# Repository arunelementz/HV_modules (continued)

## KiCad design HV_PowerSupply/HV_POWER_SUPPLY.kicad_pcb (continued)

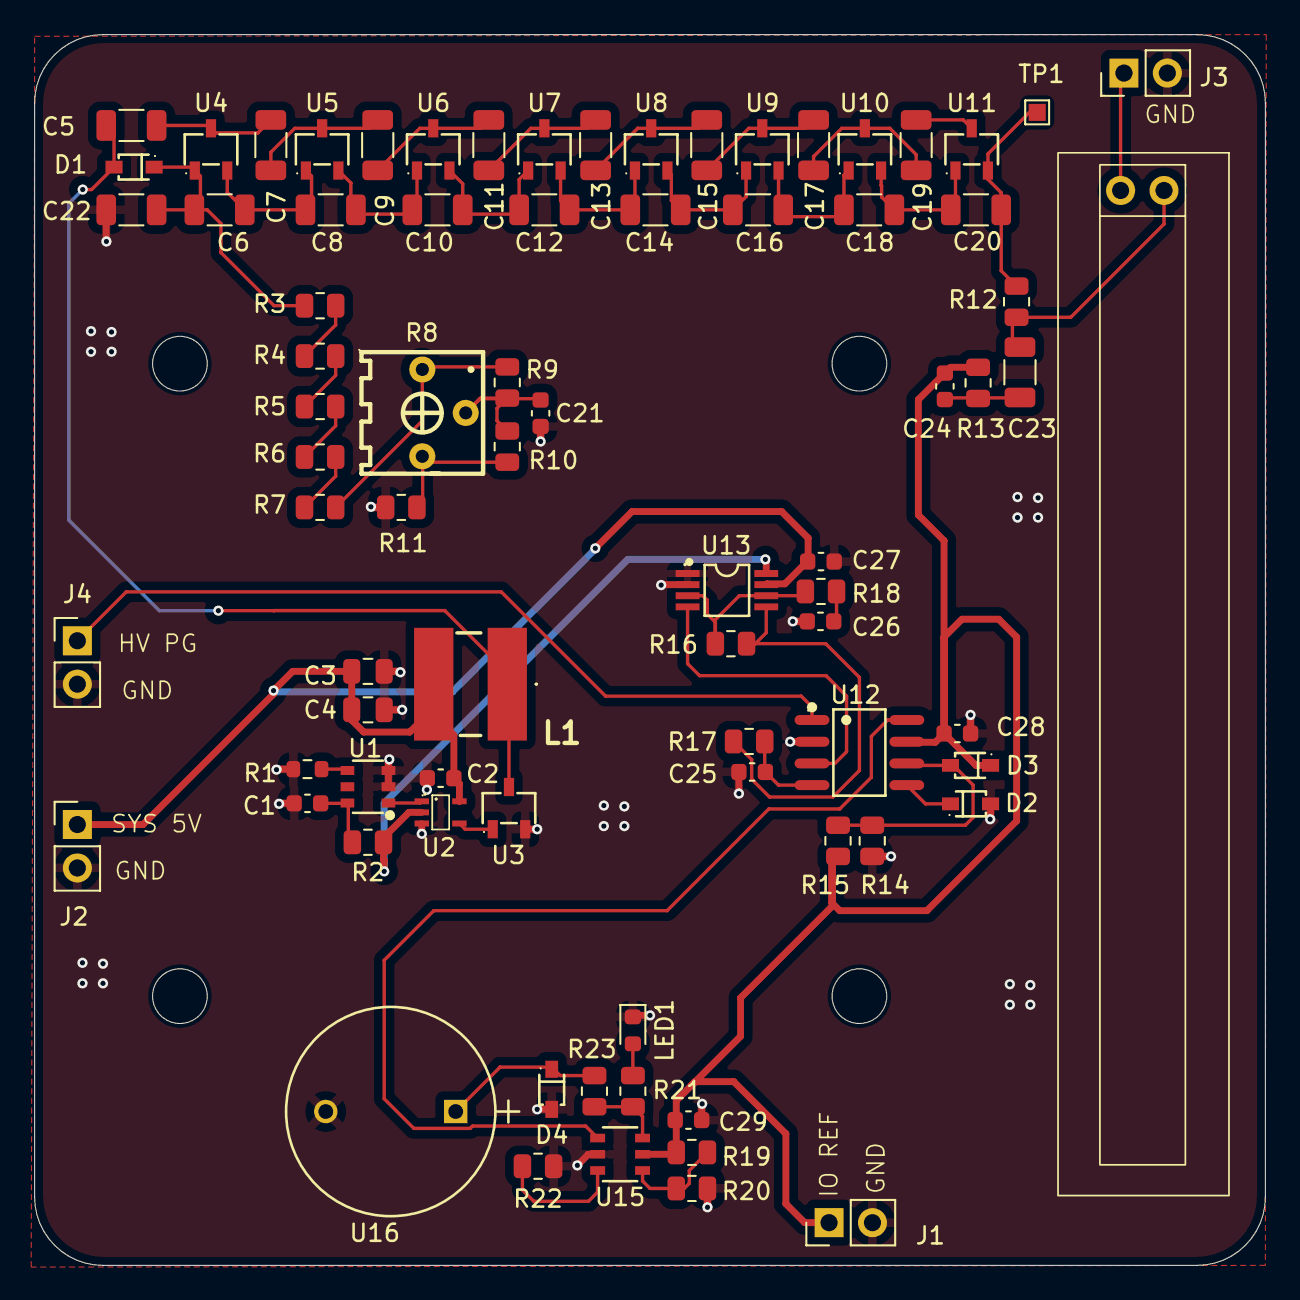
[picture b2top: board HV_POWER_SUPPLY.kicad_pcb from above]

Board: 2 copper layers, 72.0 x 72.0 mm, 83 parts (0 on the bottom side), 50 nets.

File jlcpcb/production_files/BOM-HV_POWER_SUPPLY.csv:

Comment,Designator,Footprint,LCSC
1K,R18,R_0805_2012Metric,C100046
DMN10H220L-7,U3,SOT-23-3_L2.9-W1.6-P1.90-LS2.8-BR,C102615
1Meg,"R10,R9",R_0805_2012Metric,C107700
3362P-1-205LF,R8,RES-ADJ-TH_3362P,C124582
BAS16HT1G,D4,SOD-323_L1.8-W1.3-LS2.5-RD,C131148
BAV21W-7-F,"D1,D2,D3",SOD-323_L1.8-W1.3-LS2.5-RD,C151350
1uF,"C1,C2,C26,C27,C28,C29",C_0603_1608Metric,C15849
10uF,"C3,C4",C_0805_2012Metric,C15850
100,R23,R_0805_2012Metric,C17408
200K,R13,R_0805_2012Metric,C17539
330,R21,R_0805_2012Metric,C17630
453K,"R17,R20",R_0805_2012Metric,C17702
47pF,"C21,C25",C_0603_1608Metric,C178330
221,R2,R_0805_2012Metric,C204308
127K,"R16,R19,R22",R_0805_2012Metric,C228282
TLMS1000-GS08,LED1,LED_0603_1608Metric,C2286
287K,R1,R_0603_1608Metric,C22972
0.1uF,"C10,C11,C12,C13,C14,C15,C16,C17,C18,C19,C20,C22,C5,C6,C7,C8,C9",C_1206_3216Metric,C24497
2Meg,R15,R_0805_2012Metric,C26112
3Meg,"R14,R7",R_0805_2012Metric,C2907325
2.7Meg,R11,R_0805_2012Metric,C2933390
7.5 Meg,"R12,R6",R_0805_2012Metric,C2933569
30Meg,"R3,R4,R5",R_0805_2012Metric,C317991
10pF,C23,C_1206_3216Metric,C377014
BAV23S,"U10,U11,U4,U5,U6,U7,U8,U9",BAV23S_SOT-23-3_L2.9-W1.6-P1.90-LS2.8-BR,C44345
AI-1223-TWT-5V-5-R,U16,AI-1223-TWT-5V-5-R_PUI,C5250722
SN74LVC1G08DCKR_C5279048,U2,SC-70-5_L2.0-W1.3-P0.65-LS2.1-BR,C5279048
LTC1540IMS8#PBF,U13,MSOP-8_L3.0-W3.0-P0.65-LS4.9-BL,C580397
LTC6994CS6-1-TRMPBF,U15,TSOT-23_S6_LIT,C581050
LTC1441CS8#PBF,U12,SOIC-8_L4.9-W3.8-P1.27-LS6.0-BL,C675522
LTC6906IS6#TRPBF,U1,TSOT-23-6_L2.9-W1.6-P0.95-LS2.8-BR,C689638
Conn_01x02,J1,PinHeader_1x02_P2.54mm_Vertical,
SI-29BG,U14,SI-29BG,
Conn_01x02,J3,PinHeader_1x02_P2.54mm_Vertical,
LPS6235-473MRB,L1,LPS6235473MRB,
250pF,C24,C_0603_1608Metric,
Conn_01x02,J4,PinHeader_1x02_P2.54mm_Vertical,
TestPoint,TP1,TestPoint_Pad_1.0x1.0mm,
Conn_01x02,J2,PinHeader_1x02_P2.54mm_Vertical,

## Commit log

2025-07-05 Files uploaded
2025-07-05 Into the folder
2025-07-05 done
2026-01-22 ANalog device based design folder added
2026-01-22 high voltage board
2026-01-23 Added Analog device assets
2026-01-24 -Zone clearance =.5 -added via for SYS_5V -adjust ground via
2026-01-28 Update HV_POWER_SUPPLY_NEWSHAPE-2025-12-22_160334.zip, HV_POWER_SUPPLY_NEWSHAPE-2026-01-23_200549.zip, and 3 more files...
